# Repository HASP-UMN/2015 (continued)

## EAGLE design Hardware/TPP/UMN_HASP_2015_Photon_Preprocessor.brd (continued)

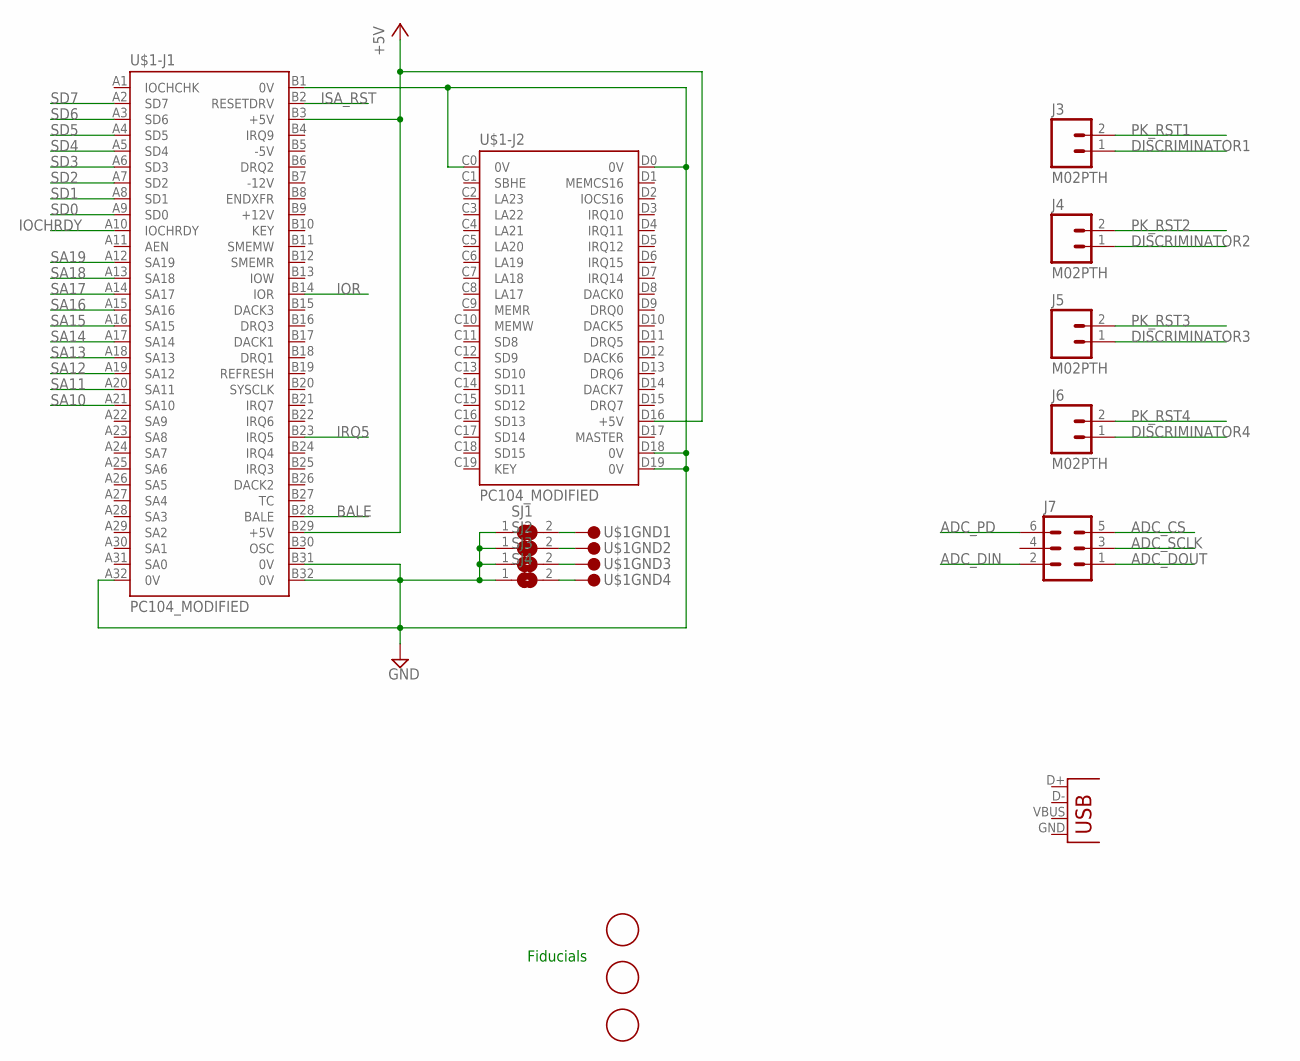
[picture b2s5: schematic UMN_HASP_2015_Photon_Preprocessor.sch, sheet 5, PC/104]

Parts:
J3, J4, J5, J6: M02PTH; 1X02
J7: MA03-2
JP5: USB-B; USB-B-PTH
SJ1, SJ2, SJ3, SJ4: SJ
U$1: PC104_MODIFIED
U$2, U$3, U$4: FIDUCIAL; FIDUCIAL_1MM

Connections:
+5V: U$1.B3 (+5V), U$1.B29 (+5V), U$1.D16 (+5V); also elsewhere on the board
ADC_CS: J7.5; also elsewhere on the board
ADC_DIN: J7.2; also elsewhere on the board
ADC_DOUT: J7.1; also elsewhere on the board
ADC_PD: J7.6
ADC_SCLK: J7.3; also elsewhere on the board
BALE: U$1.B28 (BALE); also elsewhere on the board
DISCRIMINATOR1: J3.1; also elsewhere on the board
DISCRIMINATOR2: J4.1; also elsewhere on the board
DISCRIMINATOR3: J5.1; also elsewhere on the board
DISCRIMINATOR4: J6.1; also elsewhere on the board
GND: SJ1.1, SJ2.1, SJ3.1, SJ4.1, U$1.A32 (0V), U$1.B1 (0V), U$1.B31 (0V), U$1.B32 (0V), U$1.C0 (0V), U$1.D0 (0V), U$1.D18 (0V), U$1.D19 (0V); also elsewhere on the board
IOCHRDY: U$1.A10 (IOCHRDY); also elsewhere on the board
IOR: U$1.B14 (IOR); also elsewhere on the board
IRQ5: U$1.B23 (IRQ5); also elsewhere on the board
ISA_RST: U$1.B2 (RESETDRV); also elsewhere on the board
unnamed: SJ1.2, U$1.GND@1 (1)
unnamed: SJ2.2, U$1.GND@2 (1)
unnamed: SJ3.2, U$1.GND@3 (1)
unnamed: SJ4.2, U$1.GND@4 (1)
PK_RST1: J3.2; also elsewhere on the board
PK_RST2: J4.2; also elsewhere on the board
PK_RST3: J5.2; also elsewhere on the board
PK_RST4: J6.2; also elsewhere on the board
SA10: U$1.A21 (SA10); also elsewhere on the board
SA11: U$1.A20 (SA11); also elsewhere on the board
SA12: U$1.A19 (SA12); also elsewhere on the board
SA13: U$1.A18 (SA13); also elsewhere on the board
SA14: U$1.A17 (SA14); also elsewhere on the board
SA15: U$1.A16 (SA15); also elsewhere on the board
SA16: U$1.A15 (SA16); also elsewhere on the board
SA17: U$1.A14 (SA17); also elsewhere on the board
SA18: U$1.A13 (SA18); also elsewhere on the board
SA19: U$1.A12 (SA19); also elsewhere on the board
SD0: U$1.A9 (SD0); also elsewhere on the board
SD1: U$1.A8 (SD1); also elsewhere on the board
SD2: U$1.A7 (SD2); also elsewhere on the board
SD3: U$1.A6 (SD3); also elsewhere on the board
SD4: U$1.A5 (SD4); also elsewhere on the board
SD5: U$1.A4 (SD5); also elsewhere on the board
SD6: U$1.A3 (SD6); also elsewhere on the board
SD7: U$1.A2 (SD7); also elsewhere on the board

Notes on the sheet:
Fiducials

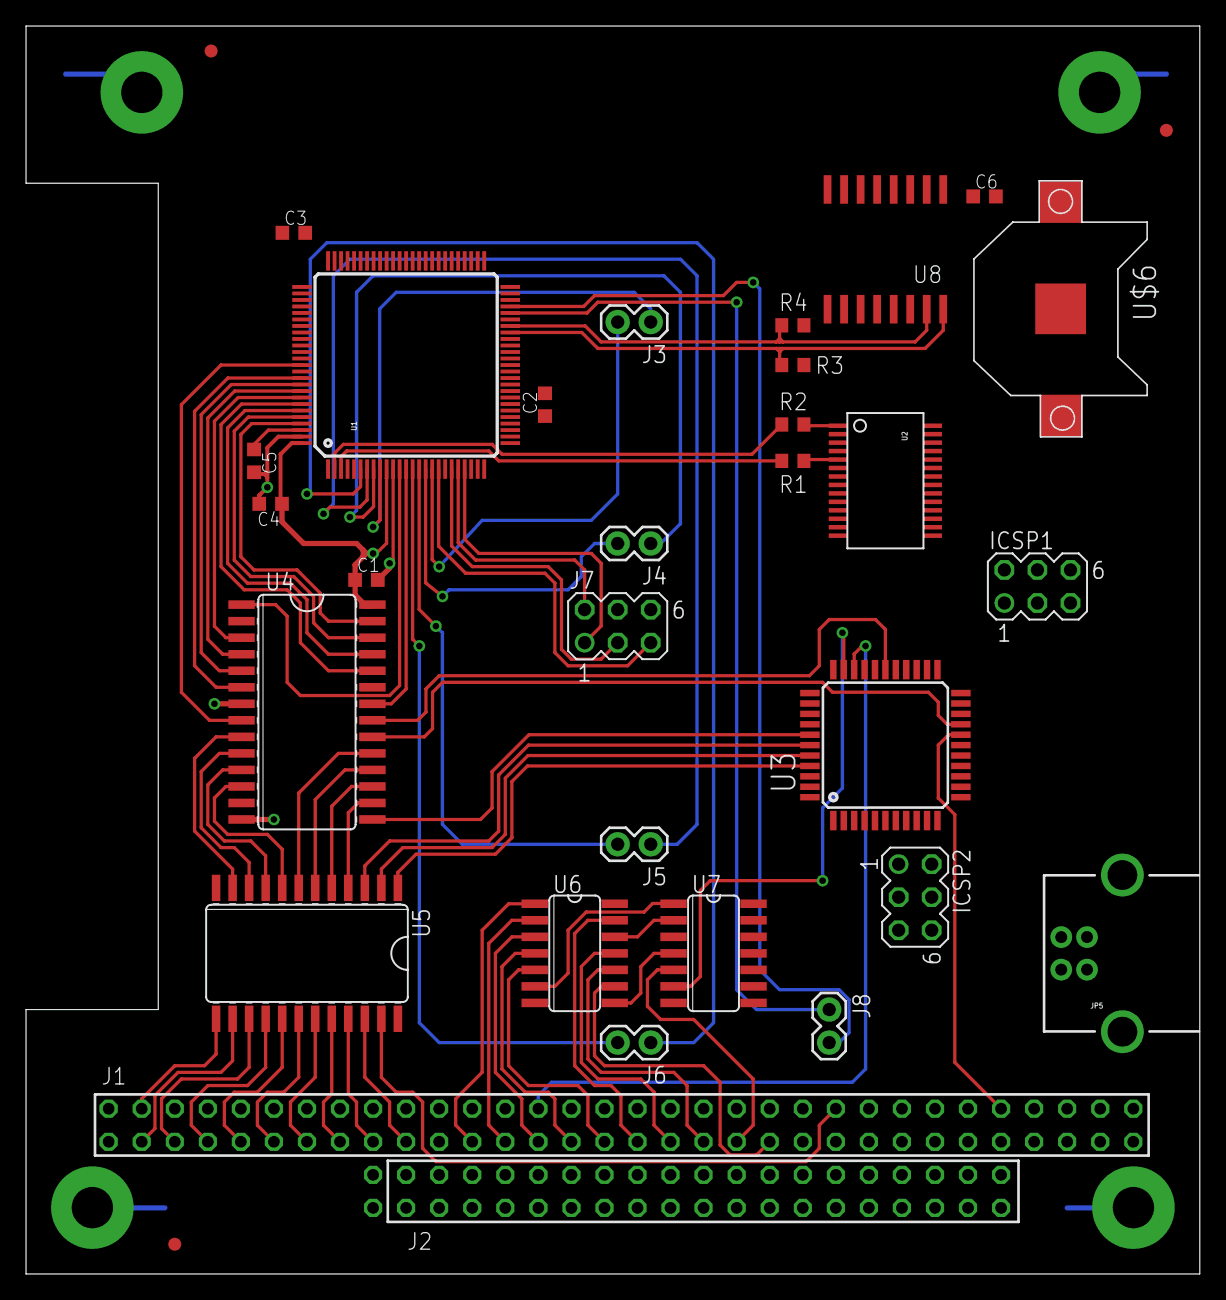
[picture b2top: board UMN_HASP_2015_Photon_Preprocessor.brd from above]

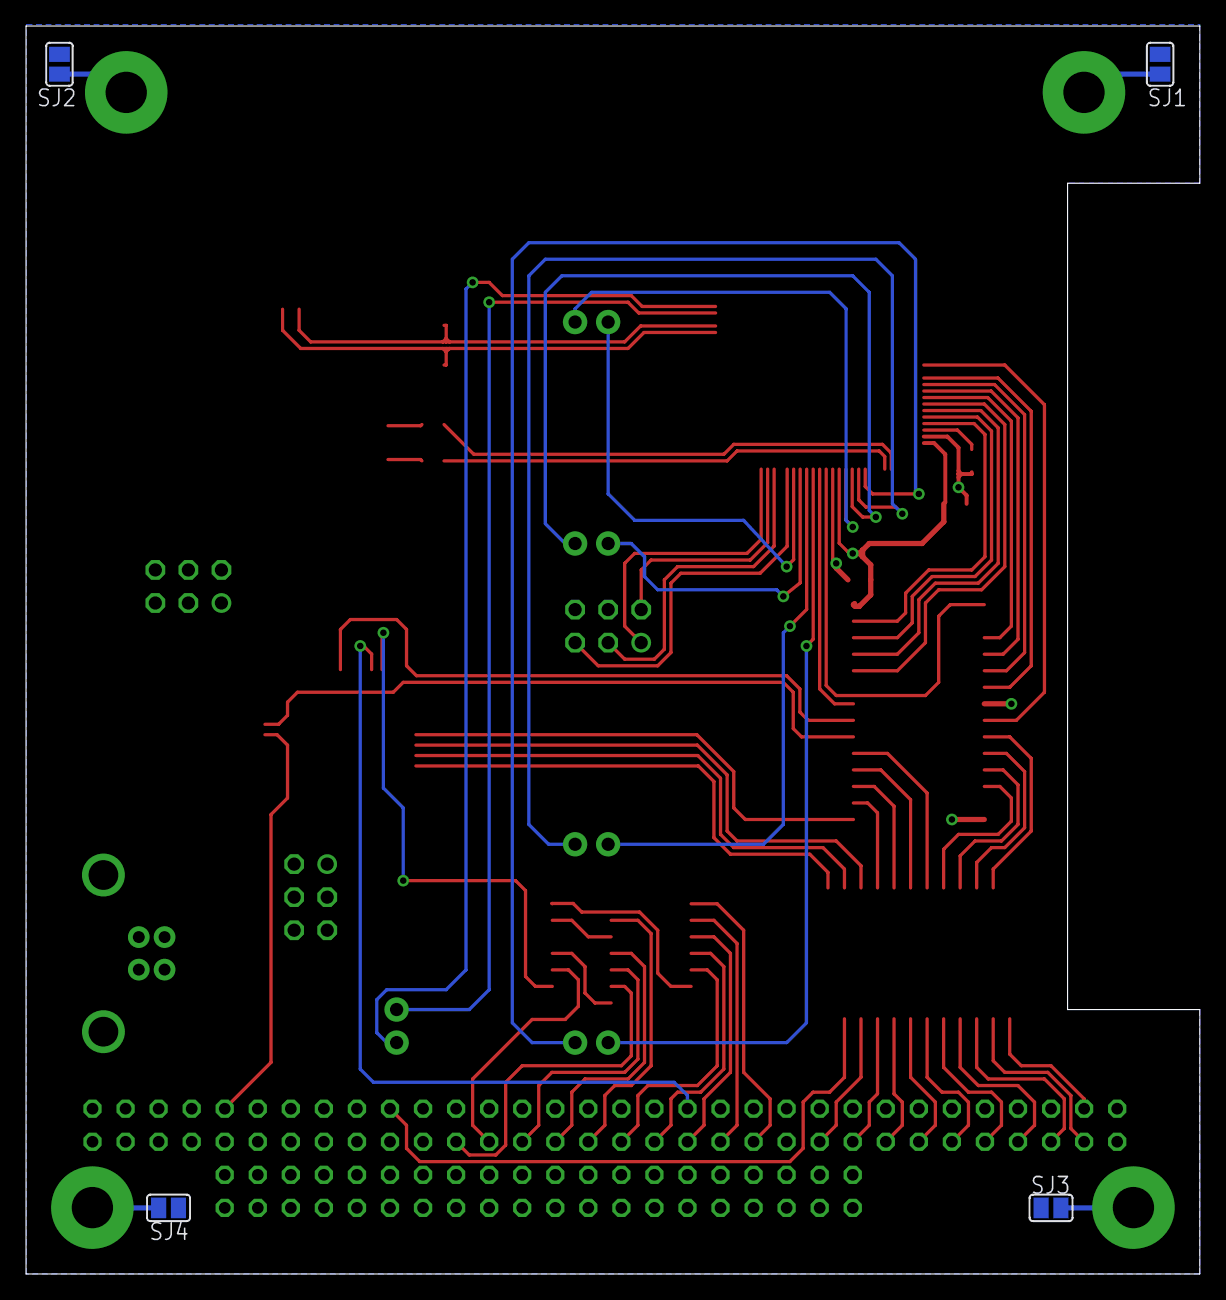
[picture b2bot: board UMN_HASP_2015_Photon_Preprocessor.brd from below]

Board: 2 copper layers, 90.2 x 95.9 mm, 36 parts (4 on the bottom side), 86 nets.

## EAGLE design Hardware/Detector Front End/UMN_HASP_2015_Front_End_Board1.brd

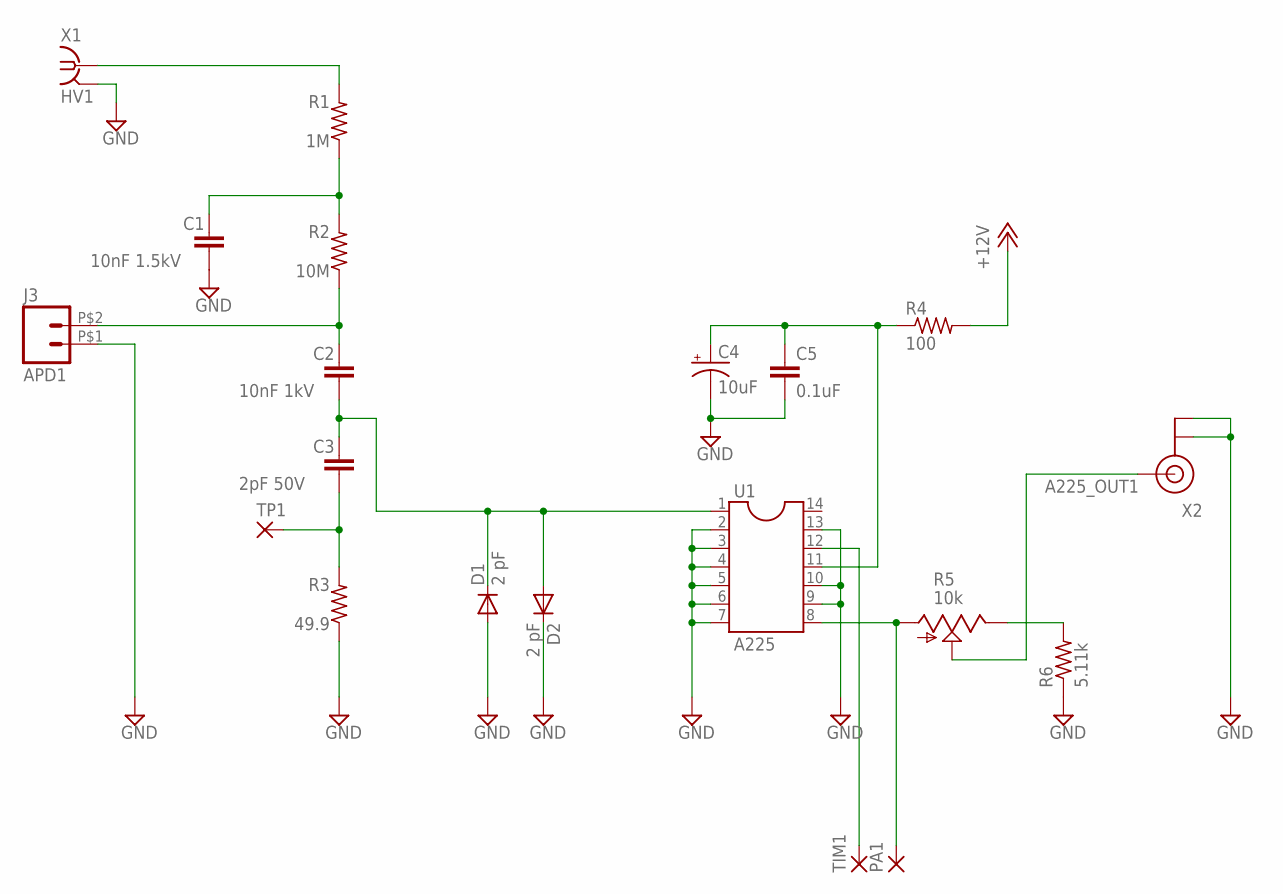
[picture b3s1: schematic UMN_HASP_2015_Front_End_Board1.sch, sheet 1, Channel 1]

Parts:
C1: 10nF 1.5kV; C1206K
C2: 10nF 1kV; C050-050X075
C3: 2pF 50V; C0402
C4: 10uF; C/6032-28R
C5: 0.1uF; C0603K
D1, D2: 2 pF; SOD323-R
J3: M02PTH2; 1X02_BIG
PA1: WIREPADSMD1,27-254; SMD1,27-2,54
R1: 1M; R1206
R2: 10M; R1206
R3: 49.9; R0603
R4: 100; R0603
R5: 10k; 3223J
R6: 5.11k; R0603
TIM1: WIREPADSMD1,27-254; SMD1,27-2,54
TP1: WIREPADSMD1,27-254; SMD1,27-2,54
U1: A225; SOCKET-14
X1: HV1; BU-SMA-V
X2: U.FL

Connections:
+12V: R4.2; also elsewhere on the board
A225_OUT1: R5.2 (S), X2.P$3 (SIGNAL)
APD1: C2.1, J3.P$2 (2), R2.1
GND: C1.2, C4.-, C5.2, D1.A, D2.C, J3.P$1 (1), R3.1, R6.1, U1.2, U1.3, U1.4, U1.5, U1.6, U1.7, U1.9, U1.10, U1.13, X1.2 (GND), X1.3 (GND), X1.4 (GND), X1.5 (GND), X2.P$1 (GND), X2.P$2 (GND); also elsewhere on the board
HV1: R1.2, X1.1
unnamed: C1.1, R1.1, R2.2
unnamed: C2.2, C3.1, D1.C, D2.A, U1.1
unnamed: R5.3 (E), R6.2
unnamed: C4.+, C5.1, R4.1, U1.11
PREAMPOUT1: PA1.1, R5.1 (A), U1.8
TIMING1: TIM1.1, U1.12
TP1: C3.2, R3.2, TP1.1

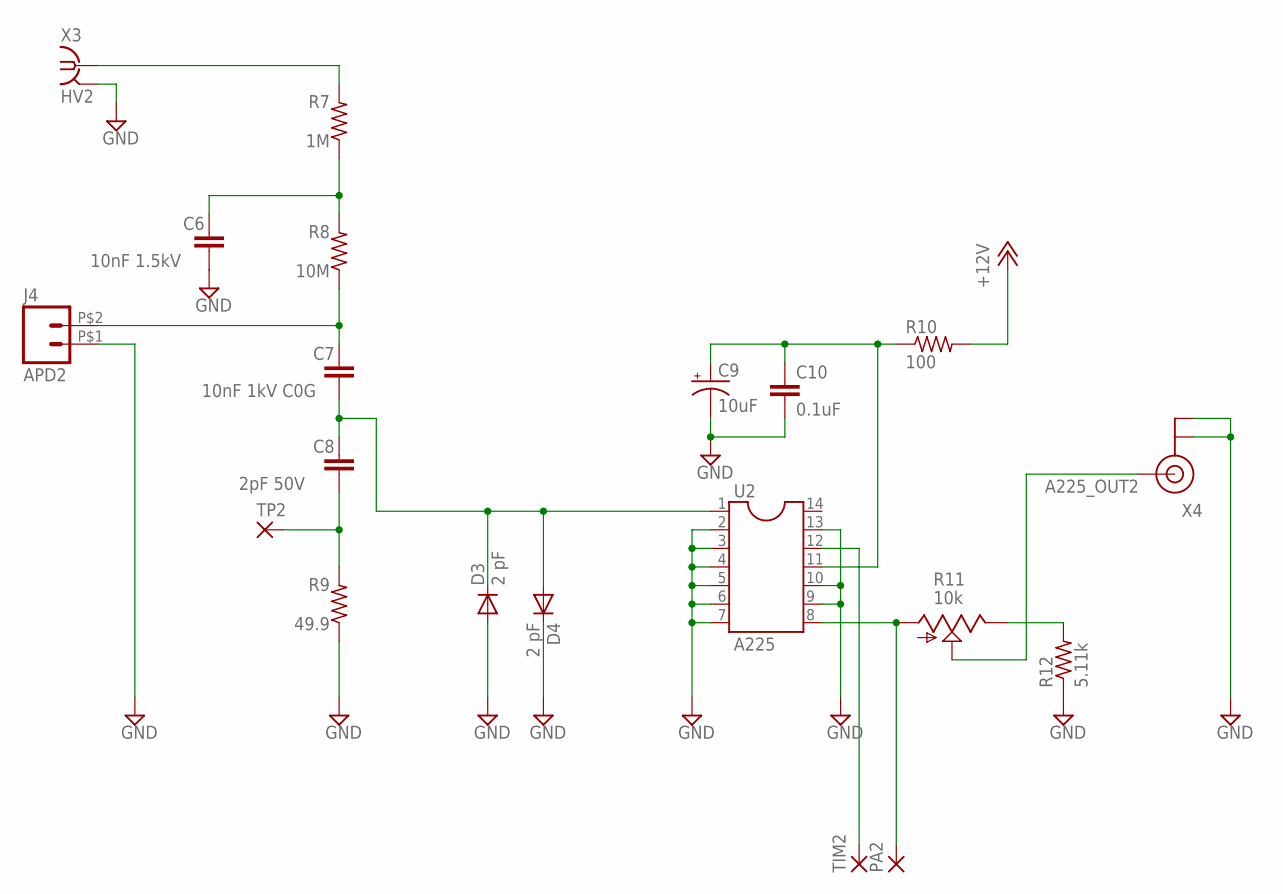
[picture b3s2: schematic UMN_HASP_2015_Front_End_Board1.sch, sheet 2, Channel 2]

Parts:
C6: 10nF 1.5kV; C1206K
C7: 10nF 1kV C0G; C050-050X075
C8: 2pF 50V; C0402
C9: 10uF; C/6032-28R
C10: 0.1uF; C0603K
D3, D4: 2 pF; SOD323-R
J4: M02PTH2; 1X02_BIG
PA2: WIREPADSMD1,27-254; SMD1,27-2,54
R7: 1M; R1206
R8: 10M; R1206
R9: 49.9; R0603
R10: 100; R0603
R11: 10k; 3223J
R12: 5.11k; R0603
TIM2: WIREPADSMD1,27-254; SMD1,27-2,54
TP2: WIREPADSMD1,27-254; SMD1,27-2,54
U2: A225; SOCKET-14
X3: HV2; BU-SMA-V
X4: U.FL

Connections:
+12V: R10.2; also elsewhere on the board
A225_OUT2: R11.2 (S), X4.P$3 (SIGNAL)
APD2: C7.1, J4.P$2 (2), R8.1
GND: C6.2, C9.-, C10.2, D3.A, D4.C, J4.P$1 (1), R9.1, R12.1, U2.2, U2.3, U2.4, U2.5, U2.6, U2.7, U2.9, U2.10, U2.13, X3.2 (GND), X3.3 (GND), X3.4 (GND), X3.5 (GND), X4.P$1 (GND), X4.P$2 (GND); also elsewhere on the board
HV2: R7.2, X3.1
unnamed: C9.+, C10.1, R10.1, U2.11
unnamed: C6.1, R7.1, R8.2
unnamed: C7.2, C8.1, D3.C, D4.A, U2.1
unnamed: R11.3 (E), R12.2
PREAMPOUT2: PA2.1, R11.1 (A), U2.8
TIMING2: TIM2.1, U2.12
TP2: C8.2, R9.2, TP2.1

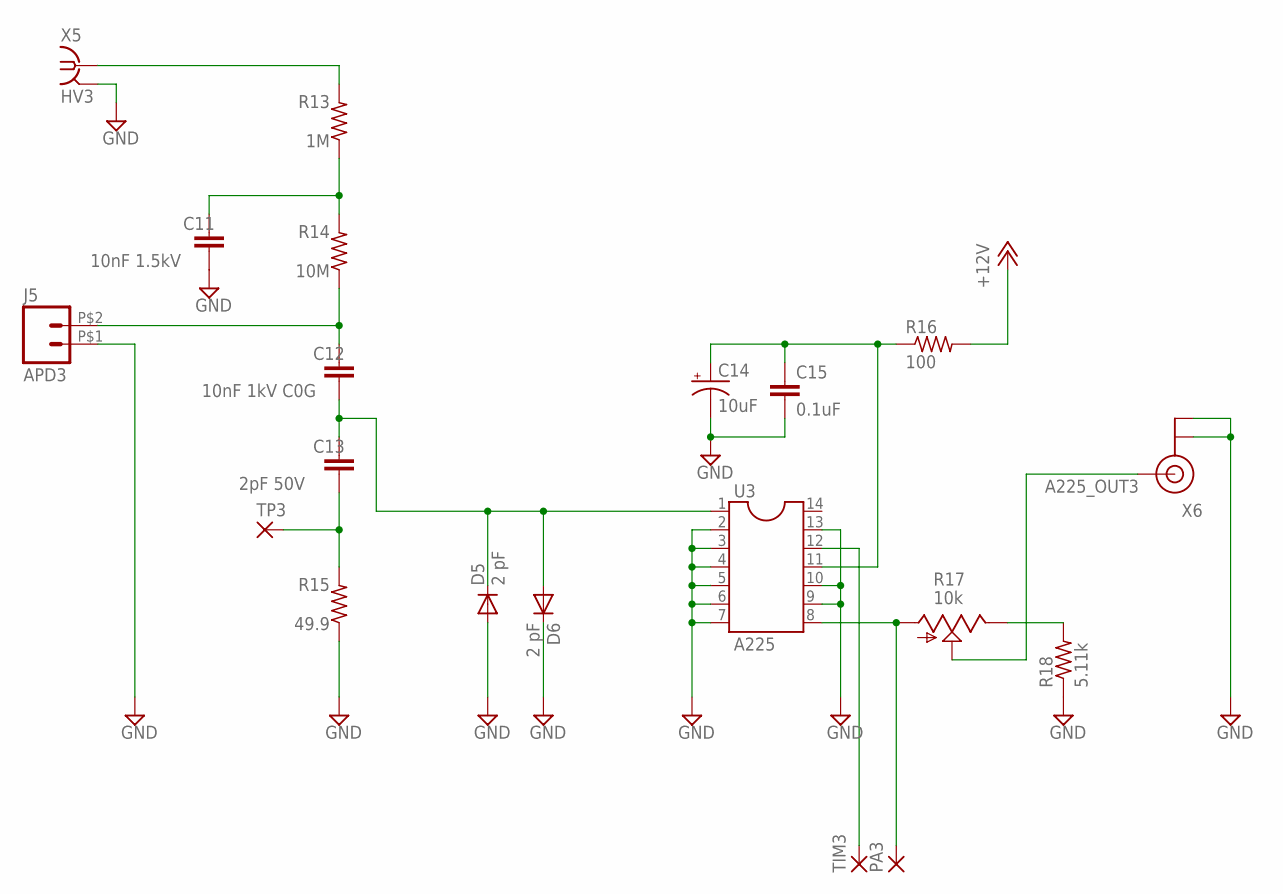
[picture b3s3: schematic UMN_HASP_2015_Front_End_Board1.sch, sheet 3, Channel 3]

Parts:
C11: 10nF 1.5kV; C1206K
C12: 10nF 1kV C0G; C050-050X075
C13: 2pF 50V; C0402
C14: 10uF; C/6032-28R
C15: 0.1uF; C0603K
D5, D6: 2 pF; SOD323-R
J5: M02PTH2; 1X02_BIG
PA3: WIREPADSMD1,27-254; SMD1,27-2,54
R13: 1M; R1206
R14: 10M; R1206
R15: 49.9; R0603
R16: 100; R0603
R17: 10k; 3223J
R18: 5.11k; R0603
TIM3: WIREPADSMD1,27-254; SMD1,27-2,54
TP3: WIREPADSMD1,27-254; SMD1,27-2,54
U3: A225; SOCKET-14
X5: HV3; BU-SMA-V
X6: U.FL

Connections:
+12V: R16.2; also elsewhere on the board
A225_OUT3: R17.2 (S), X6.P$3 (SIGNAL)
APD3: C12.1, J5.P$2 (2), R14.1
GND: C11.2, C14.-, C15.2, D5.A, D6.C, J5.P$1 (1), R15.1, R18.1, U3.2, U3.3, U3.4, U3.5, U3.6, U3.7, U3.9, U3.10, U3.13, X5.2 (GND), X5.3 (GND), X5.4 (GND), X5.5 (GND), X6.P$1 (GND), X6.P$2 (GND); also elsewhere on the board
HV3: R13.2, X5.1
unnamed: C11.1, R13.1, R14.2
unnamed: C12.2, C13.1, D5.C, D6.A, U3.1
unnamed: R17.3 (E), R18.2
unnamed: C14.+, C15.1, R16.1, U3.11
PREAMPOUT3: PA3.1, R17.1 (A), U3.8
TIMING3: TIM3.1, U3.12
TP3: C13.2, R15.2, TP3.1

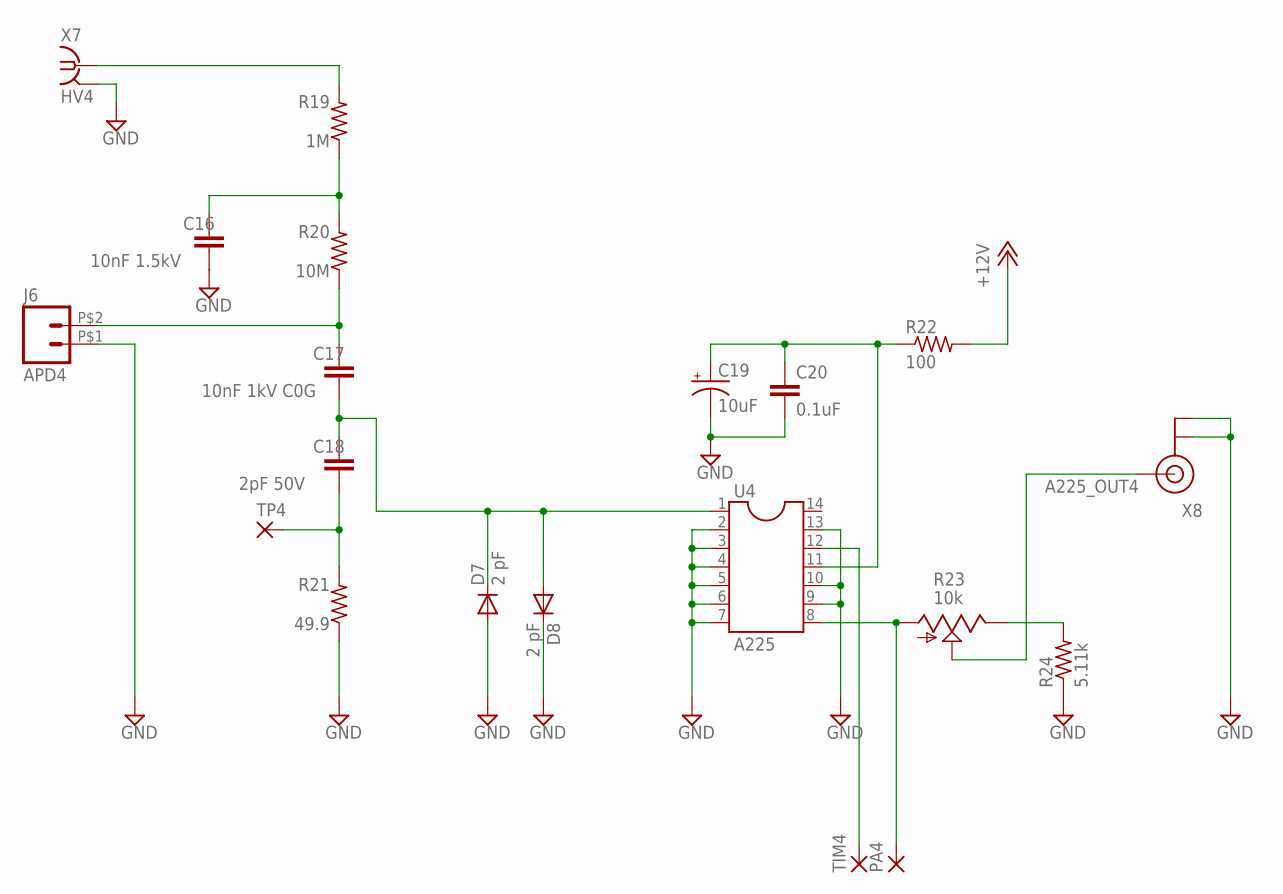
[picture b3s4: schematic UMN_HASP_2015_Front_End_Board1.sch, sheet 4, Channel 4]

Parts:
C16: 10nF 1.5kV; C1206K
C17: 10nF 1kV C0G; C050-050X075
C18: 2pF 50V; C0402
C19: 10uF; C/6032-28R
C20: 0.1uF; C0603K
D7, D8: 2 pF; SOD323-R
J6: M02PTH2; 1X02_BIG
PA4: WIREPADSMD1,27-254; SMD1,27-2,54
R19: 1M; R1206
R20: 10M; R1206
R21: 49.9; R0603
R22: 100; R0603
R23: 10k; 3223J
R24: 5.11k; R0603
TIM4: WIREPADSMD1,27-254; SMD1,27-2,54
TP4: WIREPADSMD1,27-254; SMD1,27-2,54
U4: A225; SOCKET-14
X7: HV4; BU-SMA-V
X8: U.FL

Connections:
+12V: R22.2; also elsewhere on the board
A225_OUT4: R23.2 (S), X8.P$3 (SIGNAL)
APD4: C17.1, J6.P$2 (2), R20.1
GND: C16.2, C19.-, C20.2, D7.A, D8.C, J6.P$1 (1), R21.1, R24.1, U4.2, U4.3, U4.4, U4.5, U4.6, U4.7, U4.9, U4.10, U4.13, X7.2 (GND), X7.3 (GND), X7.4 (GND), X7.5 (GND), X8.P$1 (GND), X8.P$2 (GND); also elsewhere on the board
HV4: R19.2, X7.1
unnamed: C19.+, C20.1, R22.1, U4.11
unnamed: C16.1, R19.1, R20.2
unnamed: C17.2, C18.1, D7.C, D8.A, U4.1
unnamed: R23.3 (E), R24.2
PREAMPOUT4: PA4.1, R23.1 (A), U4.8
TIMING4: TIM4.1, U4.12
TP4: C18.2, R21.2, TP4.1

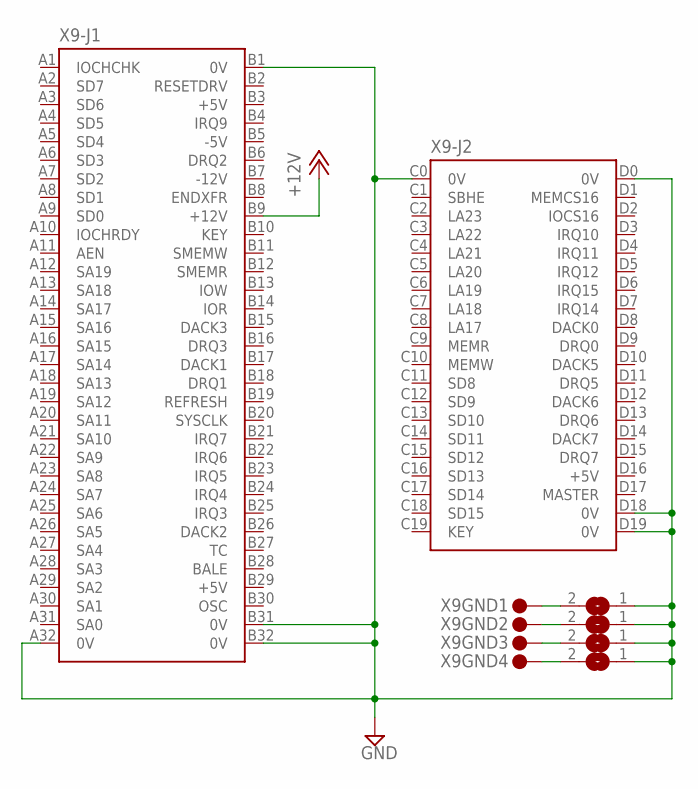
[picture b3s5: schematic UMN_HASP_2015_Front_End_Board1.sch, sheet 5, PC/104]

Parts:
SJ1, SJ2, SJ3, SJ4: SJ
X9: PC104_STANDARD1; PC104-STANDARD

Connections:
+12V: X9.B9 (+12V); also elsewhere on the board
GND: SJ1.1, SJ2.1, SJ3.1, SJ4.1, X9.A32 (0V), X9.B1 (0V), X9.B31 (0V), X9.B32 (0V), X9.C0 (0V), X9.D0 (0V), X9.D18 (0V), X9.D19 (0V); also elsewhere on the board
unnamed: SJ4.2, X9.GND@4 (1)
unnamed: SJ3.2, X9.GND@3 (1)
unnamed: SJ2.2, X9.GND@2 (1)
unnamed: SJ1.2, X9.GND@1 (1)

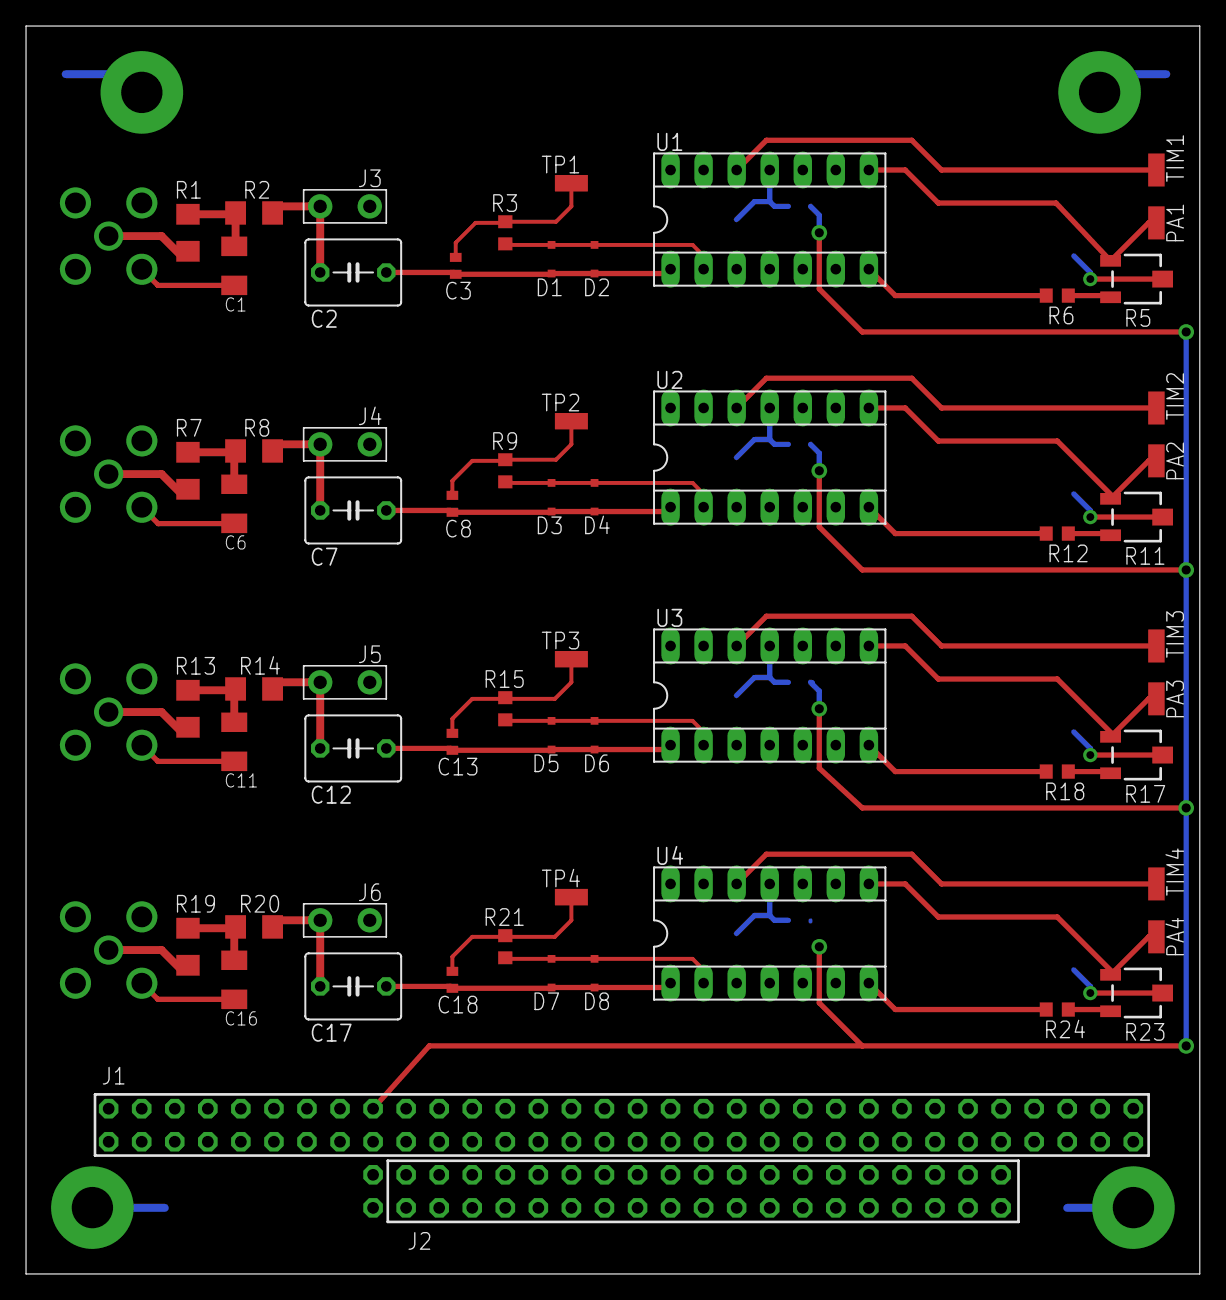
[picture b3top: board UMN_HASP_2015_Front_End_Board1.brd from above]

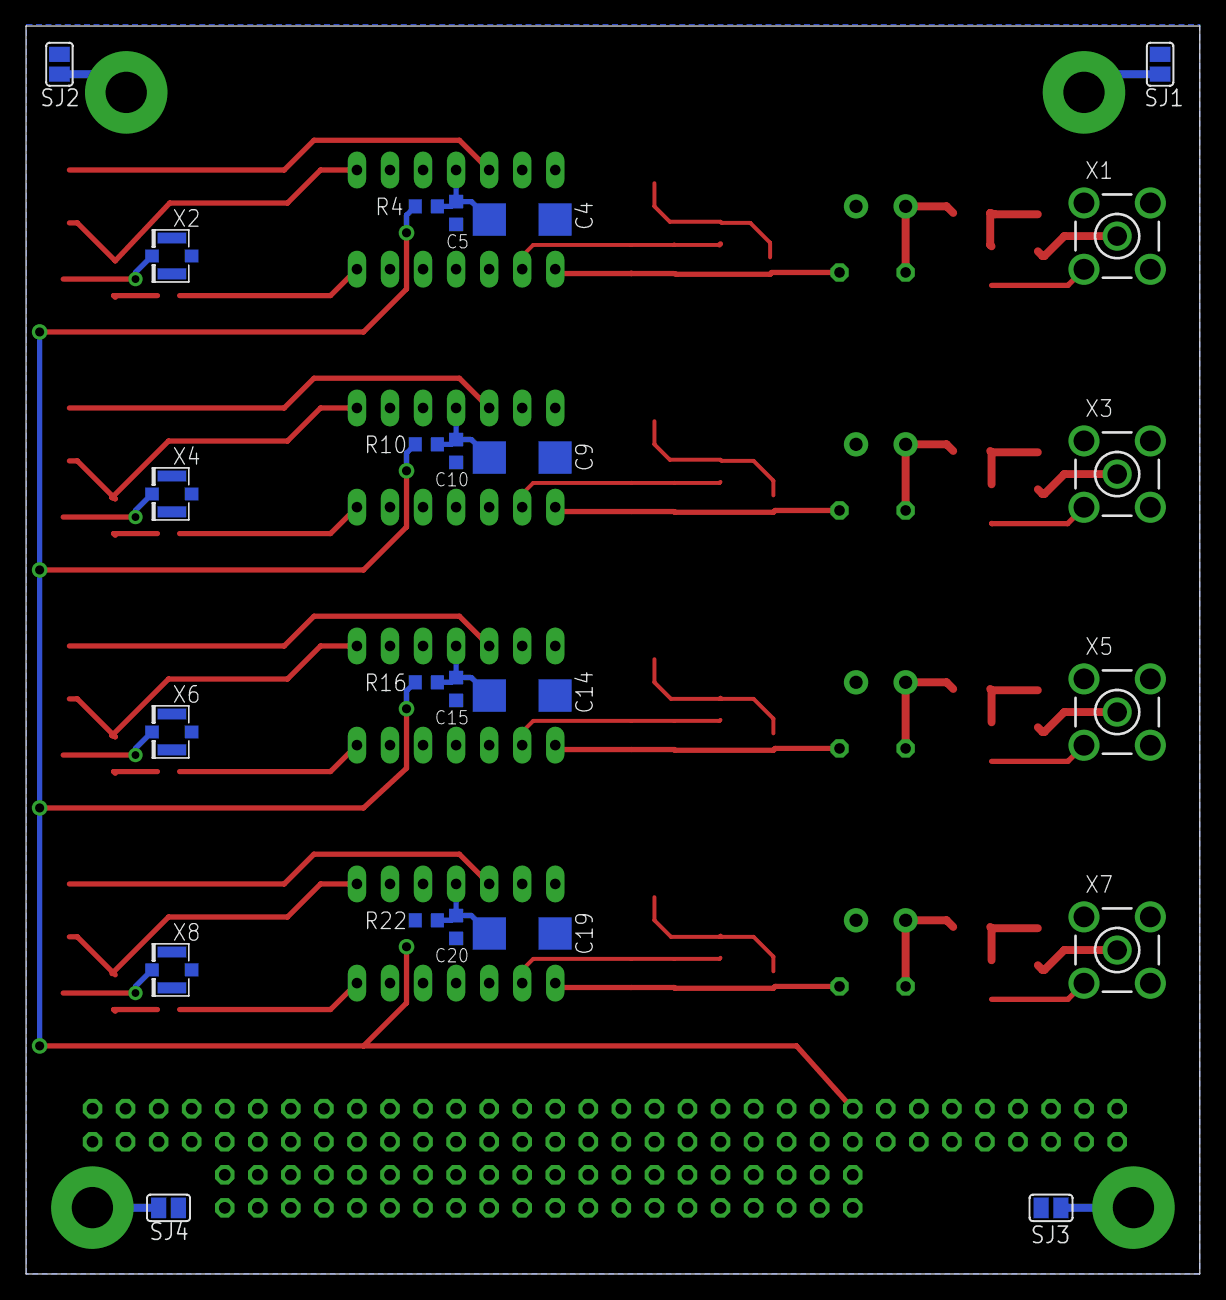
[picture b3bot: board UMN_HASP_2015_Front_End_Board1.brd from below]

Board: 2 copper layers, 90.2 x 95.9 mm, 85 parts (24 on the bottom side), 46 nets.

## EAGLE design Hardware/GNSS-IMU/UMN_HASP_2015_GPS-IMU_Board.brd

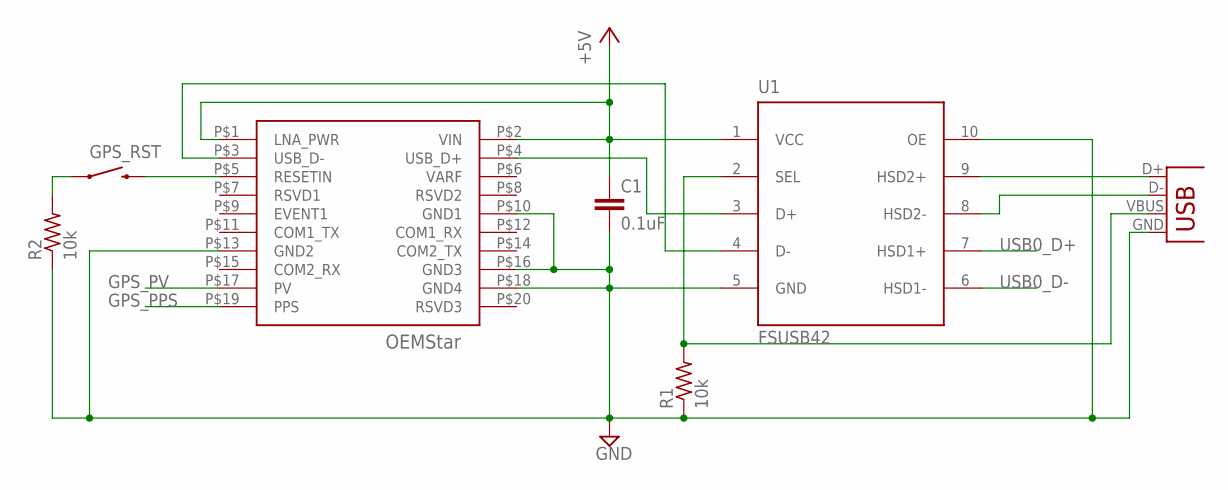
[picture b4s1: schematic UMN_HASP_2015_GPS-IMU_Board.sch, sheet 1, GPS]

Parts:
C1: 0.1uF; C1206K
GPS_RST: SWITCH-MOMENTARY-2PTH; TACTILE-PTH
J6: USB-B; USB-B-PTH
R1, R2: 10k; R1206
U1: FSUSB42; MSOP10
U$2: OEMSTAR

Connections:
+5V: C1.1, U1.1 (VCC), U$2.P$1 (LNA_PWR), U$2.P$2 (VIN); also elsewhere on the board
GND: C1.2, J6.GND, R1.1, R2.1, U1.5 (GND), U1.10 (OE), U$2.P$10 (GND1), U$2.P$13 (GND2), U$2.P$16 (GND3), U$2.P$18 (GND4); also elsewhere on the board
GPS_PPS: U$2.P$19 (PPS); also elsewhere on the board
GPS_PV: U$2.P$17 (PV); also elsewhere on the board
unnamed: GPS_RST.1, R2.2
unnamed: J6.D-, U1.8 (HSD2-)
unnamed: J6.VBUS, R1.2, U1.2 (SEL)
unnamed: GPS_RST.3 (2), U$2.P$5 (RESETIN)
unnamed: U1.3 (D+), U$2.P$4 (USB_D+)
unnamed: U1.4 (D-), U$2.P$3 (USB_D-)
unnamed: J6.D+, U1.9 (HSD2+)
USB0_D+: U1.7 (HSD1+); also elsewhere on the board
USB0_D-: U1.6 (HSD1-); also elsewhere on the board

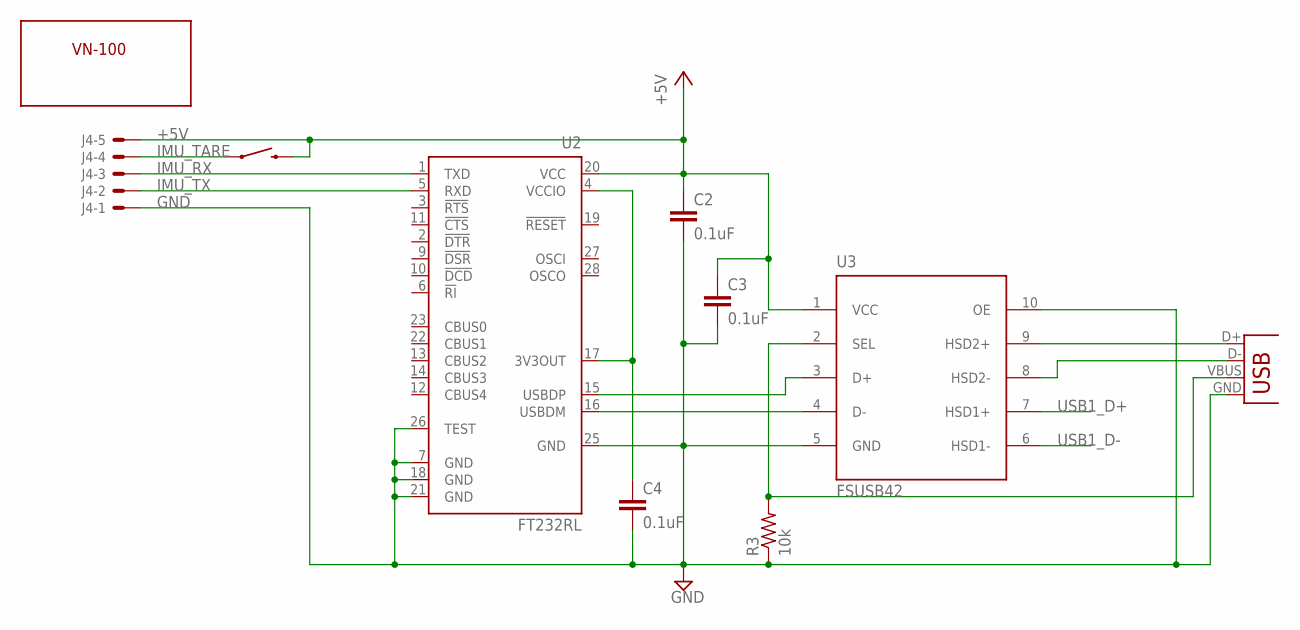
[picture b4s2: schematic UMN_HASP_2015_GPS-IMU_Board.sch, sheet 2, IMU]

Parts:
C2, C3, C4: 0.1uF; C1206K
IMU_TARE: SWITCH-MOMENTARY-2PTH; TACTILE-PTH
J4: C-GRID-05-70553; 70553-05
J5: USB-B; USB-B-PTH
R3: 10k; R1206
U2: FT232RL; SSOP28
U3: FSUSB42; MSOP10
U$3: VN-100

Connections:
+5V: C2.1, C3.1, IMU_TARE.3 (2), J4.5, U2.20 (VCC), U3.1 (VCC); also elsewhere on the board
GND: C2.2, C3.2, C4.2, J4.1, J5.GND, R3.1, U2.7 (GND), U2.18 (GND), U2.21 (GND), U2.25 (GND), U2.26 (TEST), U3.5 (GND), U3.10 (OE); also elsewhere on the board
IMU_RX: J4.3, U2.1 (TXD)
IMU_TARE: IMU_TARE.1, J4.4
IMU_TX: J4.2, U2.5 (RXD)
unnamed: J5.D+, U3.9 (HSD2+)
unnamed: U2.16 (USBDM), U3.4 (D-)
unnamed: U2.15 (USBDP), U3.3 (D+)
unnamed: J5.D-, U3.8 (HSD2-)
unnamed: J5.VBUS, R3.2, U3.2 (SEL)
unnamed: C4.1, U2.4 (VCCIO), U2.17 (3V3OUT)
USB1_D+: U3.7 (HSD1+); also elsewhere on the board
USB1_D-: U3.6 (HSD1-); also elsewhere on the board

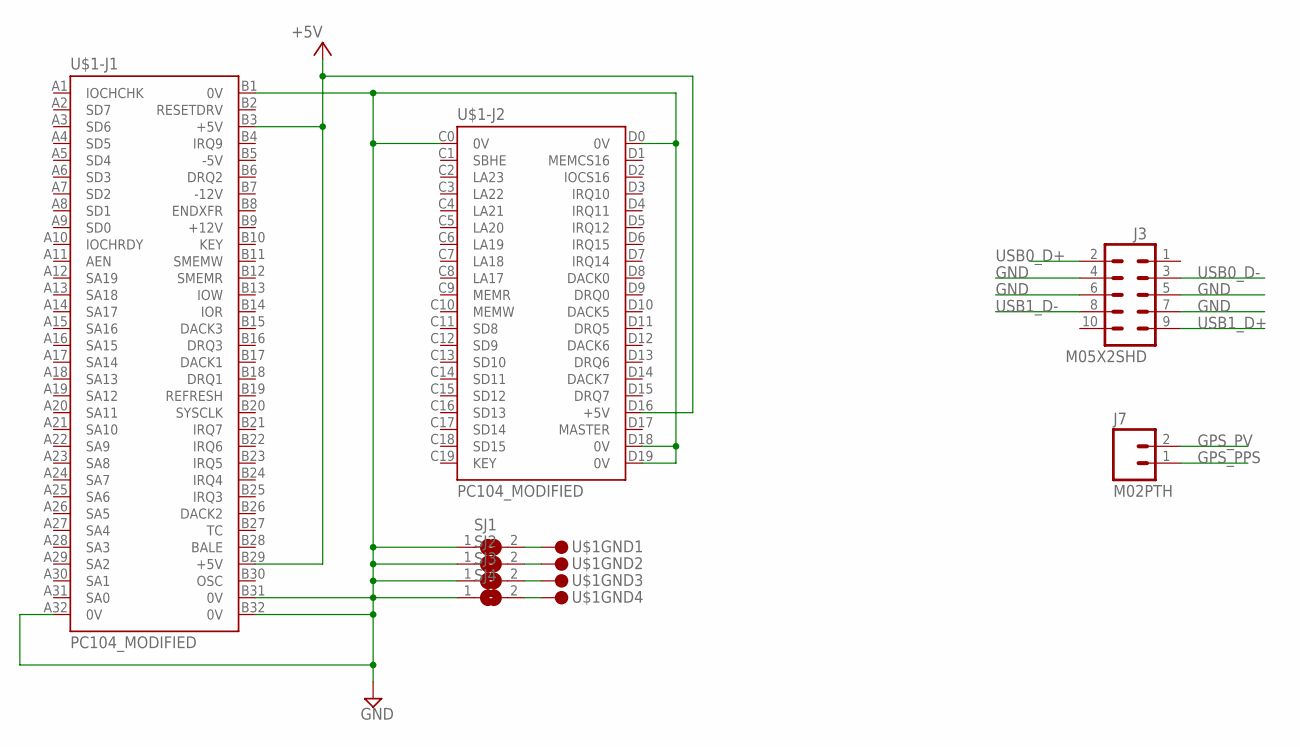
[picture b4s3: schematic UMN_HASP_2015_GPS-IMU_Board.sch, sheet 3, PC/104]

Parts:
J3: M05X2SHD; 2X5-SHROUDED
J7: M02PTH; 1X02
SJ1, SJ2, SJ3, SJ4: SJ
U$1: PC104_MODIFIED

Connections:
+5V: U$1.B3 (+5V), U$1.B29 (+5V), U$1.D16 (+5V); also elsewhere on the board
GND: J3.4, J3.5, J3.6, J3.7, SJ1.1, SJ2.1, SJ3.1, SJ4.1, U$1.A32 (0V), U$1.B1 (0V), U$1.B31 (0V), U$1.B32 (0V), U$1.C0 (0V), U$1.D0 (0V), U$1.D18 (0V), U$1.D19 (0V); also elsewhere on the board
GPS_PPS: J7.1; also elsewhere on the board
GPS_PV: J7.2; also elsewhere on the board
unnamed: SJ1.2, U$1.GND@1 (1)
unnamed: SJ2.2, U$1.GND@2 (1)
unnamed: SJ3.2, U$1.GND@3 (1)
unnamed: SJ4.2, U$1.GND@4 (1)
USB0_D+: J3.2; also elsewhere on the board
USB0_D-: J3.3; also elsewhere on the board
USB1_D+: J3.9; also elsewhere on the board
USB1_D-: J3.8; also elsewhere on the board
